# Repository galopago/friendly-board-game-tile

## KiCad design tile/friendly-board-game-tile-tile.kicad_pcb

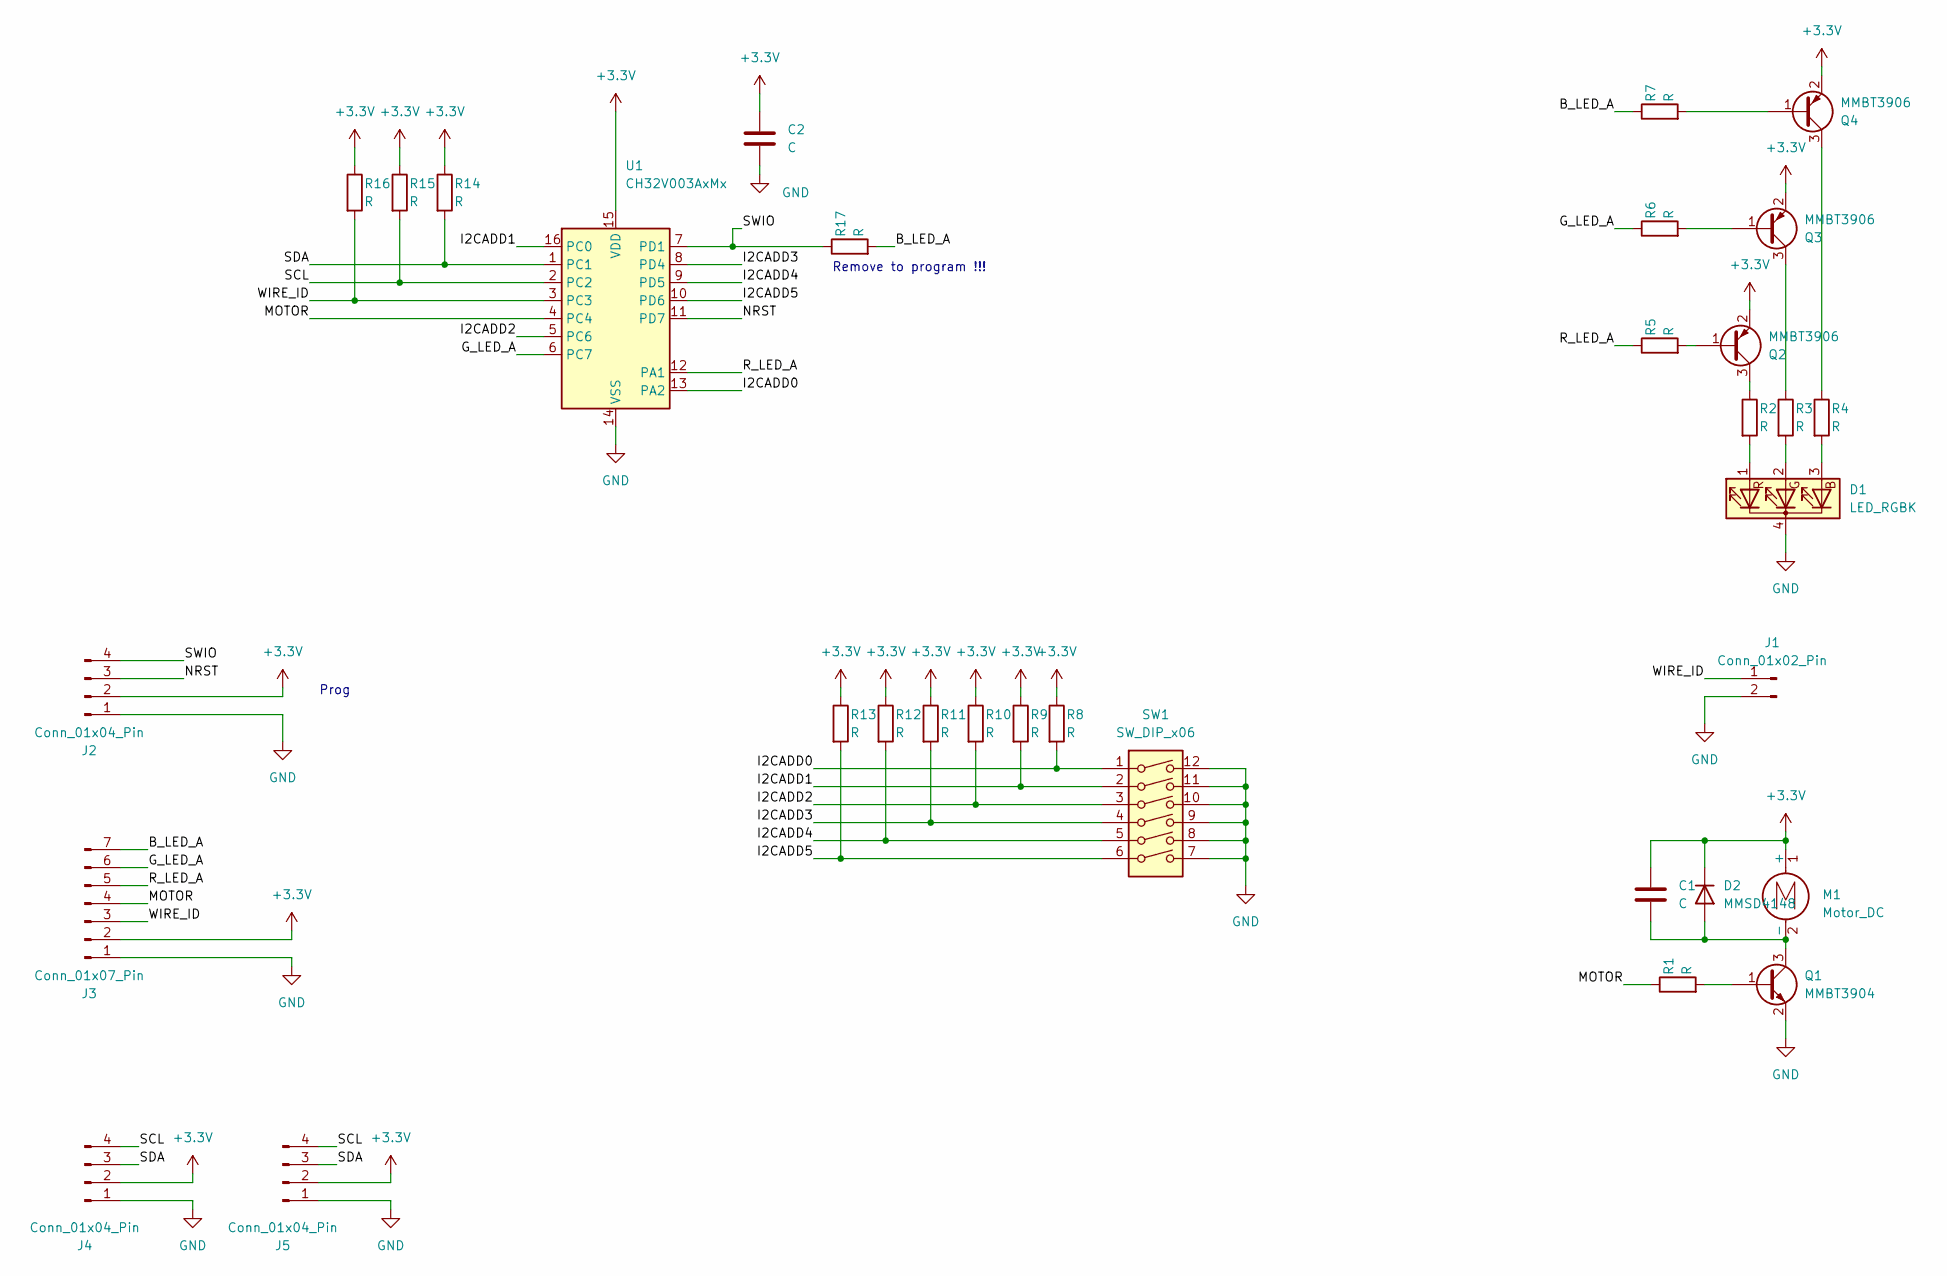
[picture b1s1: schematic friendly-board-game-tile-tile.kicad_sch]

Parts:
C1, C2: C; C_0805_2012Metric_Pad1.18x1.45mm_HandSolder
D1: LED_RGBK; LED_RGB_Wuerth-PLCC4_3.2x2.8mm_150141M173100
D2: MMSD4148; D_SOD-123
J1: Conn_01x02_Pin; Connector_6mm_1_Pin
J2, J4, J5: Conn_01x04_Pin; PinHeader_1x04_P2.54mm_Vertical
J3: Conn_01x07_Pin; PinHeader_1x07_P2.54mm_Vertical
M1: Motor_DC; 12x6mm wired vibrating motor
Q1: MMBT3904; SOT-23
Q2, Q3, Q4: MMBT3906; SOT-23
R1, R2, R3, R4, R5, R6, R7, R8, R9, R10, R11, R12, R13, R14, R15, R16, R17: R; R_0805_2012Metric_Pad1.20x1.40mm_HandSolder
SW1: SW_DIP_x06; SW_DIP_SPSTx06_Slide_6.7x16.8mm_W8.61mm_P2.54mm_LowProfile
U1: CH32V003AxMx; SOP-16_3.9x9.9mm_P1.27mm

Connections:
+3.3V: C1.1, C2.1, D2.1 (K), J2.2, J3.2, J4.2, J5.2, M1.1 (+), Q2.2 (E), Q3.2 (E), Q4.2 (E), R8.1, R9.1, R10.1, R11.1, R12.1, R13.1, R14.1, R15.1, R16.1, U1.15 (VDD)
/B_LED_A: J3.7, R7.1, R17.2
/G_LED_A: J3.6, R6.1, U1.6 (PC7)
/I2CADD0: R8.2, SW1.1, U1.13 (PA2)
/I2CADD1: R9.2, SW1.2, U1.16 (PC0)
/I2CADD2: R10.2, SW1.3, U1.5 (PC6)
/I2CADD3: R11.2, SW1.4, U1.8 (PD4)
/I2CADD4: R12.2, SW1.5, U1.9 (PD5)
/I2CADD5: R13.2, SW1.6, U1.10 (PD6)
/MOTOR: J3.4, R1.1, U1.4 (PC4)
/NRST: J2.3, U1.11 (PD7)
/R_LED_A: J3.5, R5.1, U1.12 (PA1)
/SCL: J4.4, J5.4, R15.2, U1.2 (PC2)
/SDA: J4.3, J5.3, R14.2, U1.1 (PC1)
/SWIO: J2.4, R17.1, U1.7 (PD1)
/WIRE_ID: J1.1, J3.3, R16.2, U1.3 (PC3)
GND: C2.2, D1.4 (K), J1.2, J2.1, J3.1, J4.1, J5.1, Q1.2 (E), SW1.7, SW1.8, SW1.9, SW1.10, SW1.11, SW1.12, U1.14 (VSS)
unnamed: D1.3 (BA), R4.2
unnamed: D1.2 (GA), R3.2
unnamed: D1.1 (RA), R2.2
unnamed: C1.2, D2.2 (A), M1.2 (-), Q1.3 (C)
unnamed: Q1.1 (B), R1.2
unnamed: Q2.1 (B), R5.2
unnamed: Q2.3 (C), R2.1
unnamed: Q3.1 (B), R6.2
unnamed: Q3.3 (C), R3.1
unnamed: Q4.1 (B), R7.2
unnamed: Q4.3 (C), R4.1

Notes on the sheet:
Remove to program !!!
Prog

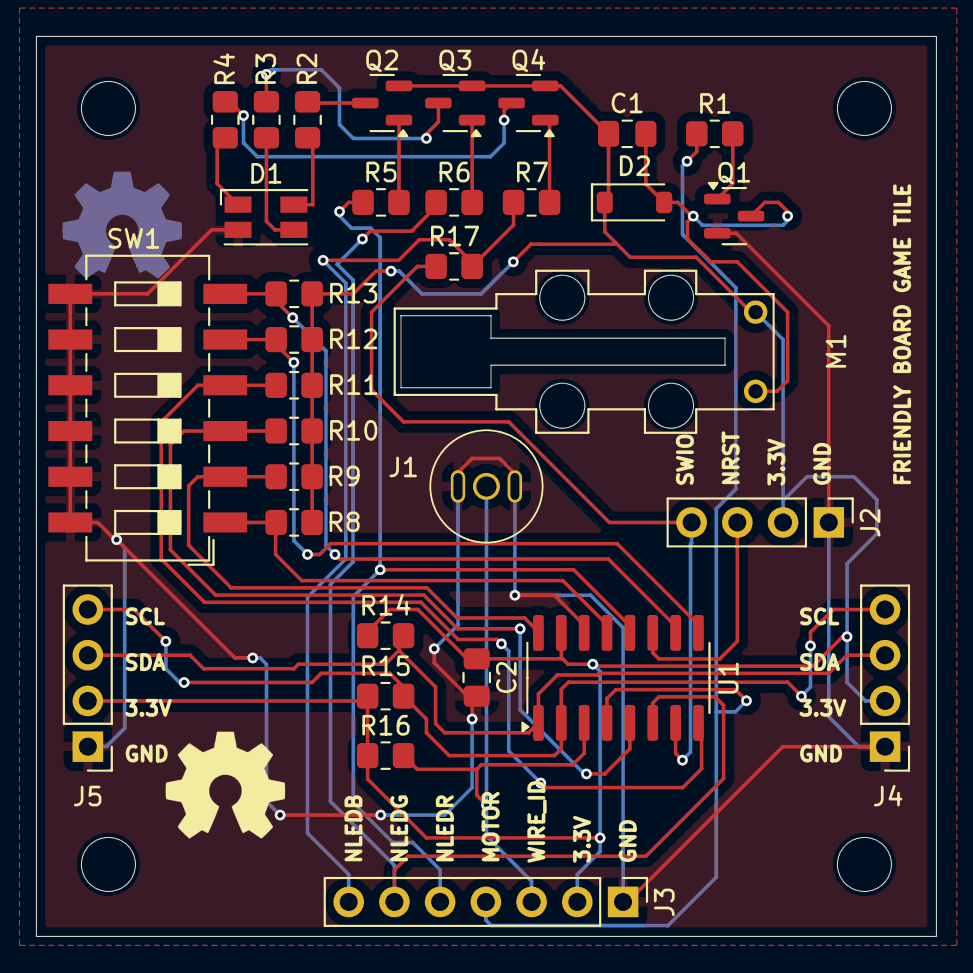
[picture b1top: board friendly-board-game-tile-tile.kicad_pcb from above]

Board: 2 copper layers, 50.0 x 50.0 mm, 37 parts (0 on the bottom side), 28 nets.

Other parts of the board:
MH01, MH02, MH03, MH04: MountingHole_3mm

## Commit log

2026-03-16 Add game piece board: PCB with routed traces for clues
2026-03-16 Add Gerber files for single game piece PCB
2026-03-16 Fix game piece PCB dimensions to make board symmetric
2026-03-16 Update single-board Gerber files with corrected dimensions
2026-03-16 Add panelized PCB Gerber files for multiple game piece boards
2026-03-17 Tile card routed with silkscreens
2026-03-18 Add Gerber files for single tile card
2026-03-18 Add Gerber files for panel of tile cards
